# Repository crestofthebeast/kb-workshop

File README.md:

# kb-workshop
keyboards and such

here be dragons!

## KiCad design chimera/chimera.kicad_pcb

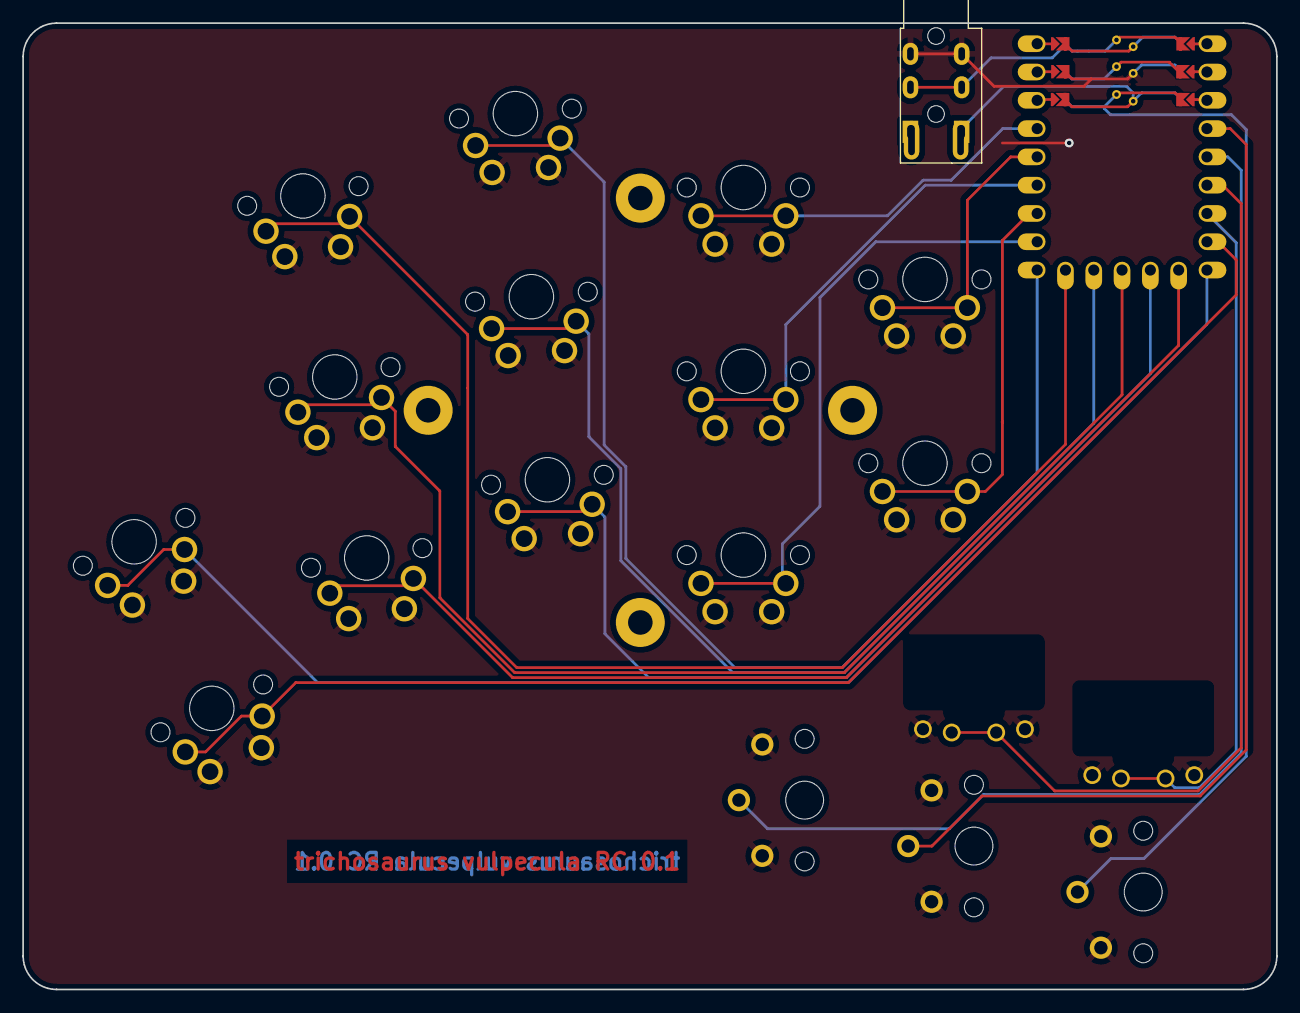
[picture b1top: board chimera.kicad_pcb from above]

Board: 2 copper layers, 112.6 x 86.8 mm, 15 parts (0 on the bottom side), 14 nets.

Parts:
J2: Serial; Jack_3.5mm_PJ320E_Horizontal_reversible
S1, S2, S3, S4, S5, S6, S7, S8, S9, S10, S11, S12, S13: MX
U?: rp2040-zero-tht

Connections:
GND: J2.R2, S1.1, S2.1, S3.1, S4.1, S5.1, S6.1, S7.1, S8.1, S9.1, S10.1, S11.1, S12.1, S13.1
matrix_index_bottom: S9.2, U?.16
matrix_index_home: S10.2, U?.18
matrix_index_top: S11.2, U?.20
matrix_inner_home: S12.2, U?.17
matrix_inner_top: S13.2, U?.19
matrix_middle_bottom: S6.2, U?.11
matrix_middle_home: S7.2, U?.13
matrix_middle_top: S8.2, U?.15
matrix_pinky_home: S1.2, U?.8
matrix_pinky_top: S2.2, U?.9
matrix_ring_bottom: S3.2, U?.10
matrix_ring_home: S4.2, U?.12
matrix_ring_top: S5.2, U?.14

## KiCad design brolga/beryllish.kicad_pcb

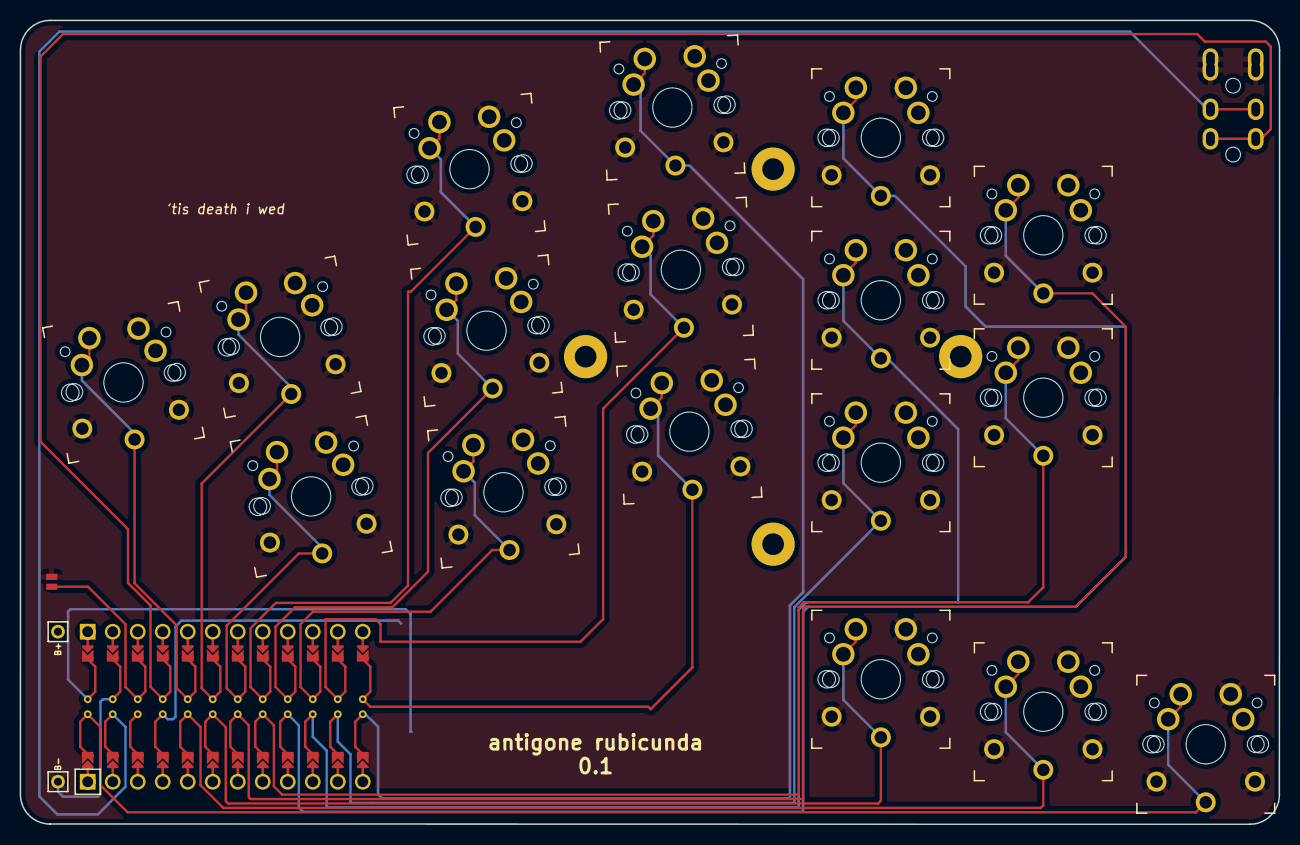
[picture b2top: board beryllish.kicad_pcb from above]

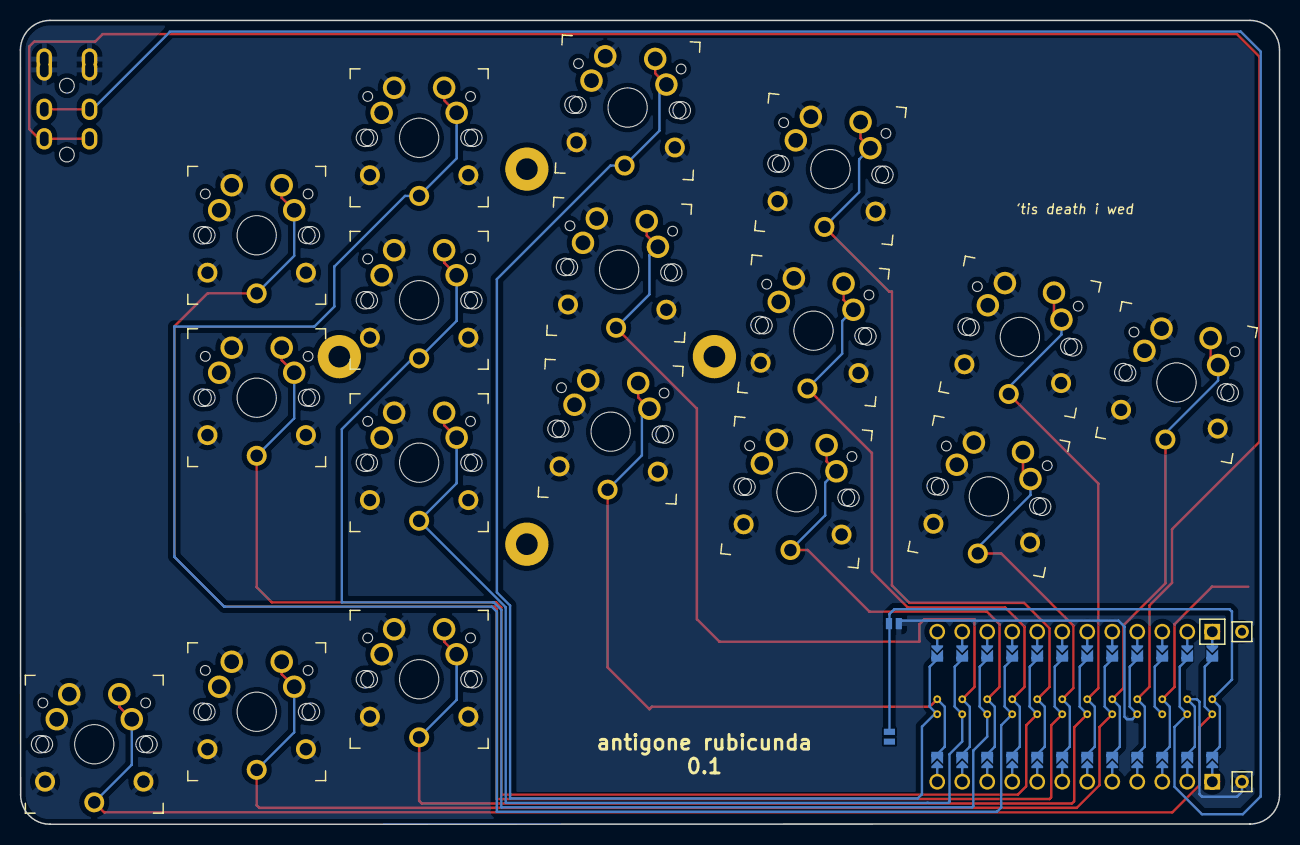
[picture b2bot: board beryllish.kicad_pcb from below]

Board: 2 copper layers, 127.9 x 81.7 mm, 23 parts (2 on the bottom side), 20 nets.

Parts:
B+: MountingHole_Pad; 1pin_conn
B-: MountingHole_Pad; 1pin_conn
J1, J2, J3: Jumper
MCU1: ProMicro
S1, S2, S3, S4, S5, S6, S7, S8, S9, S10, S11, S12, S13, S14, S15, S16, S17: SW_MX_choc

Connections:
GND: B-.1, J2.1, J3.1, MCU1.2, MCU1.21, MCU1.22, S1.2, S2.2, S3.2, S4.2, S5.2, S6.2, S7.2, S8.2, S9.2, S10.2, S11.2, S12.2, S13.2, S14.2, S15.2, S16.2, S17.2
RAW: J1.1, J1.2, J2.2, MCU1.1
RESET: J3.2, MCU1.3
SW1: MCU1.18, S14.1
SW2: MCU1.17, S13.1
SW3: MCU1.16, S12.1
SW4: MCU1.15, S11.1
SW5: MCU1.14, S10.1
SW6: MCU1.13, S9.1
SW7: MCU1.11, S8.1
SW8: MCU1.12, S7.1
SW9: MCU1.8, S6.1
SW10: MCU1.9, S5.1
SW11: MCU1.10, S4.1
SW12: MCU1.5, S1.1
SW13: MCU1.6, S3.1
SW14: MCU1.7, S2.1
SW15: MCU1.19, S15.1
SW16: MCU1.20, S16.1
SW17: MCU1.24, S17.1

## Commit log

2022-06-23 init
2022-06-23 fixes
2022-06-23 minor refactor
2022-06-23 more fixes
2022-06-27 lim chimera
2022-06-27 fix lc
2022-06-27 manifold-isation
2022-06-29 move tentig puck a little
2022-07-04 chimera
2022-07-04 humtyl first pass
